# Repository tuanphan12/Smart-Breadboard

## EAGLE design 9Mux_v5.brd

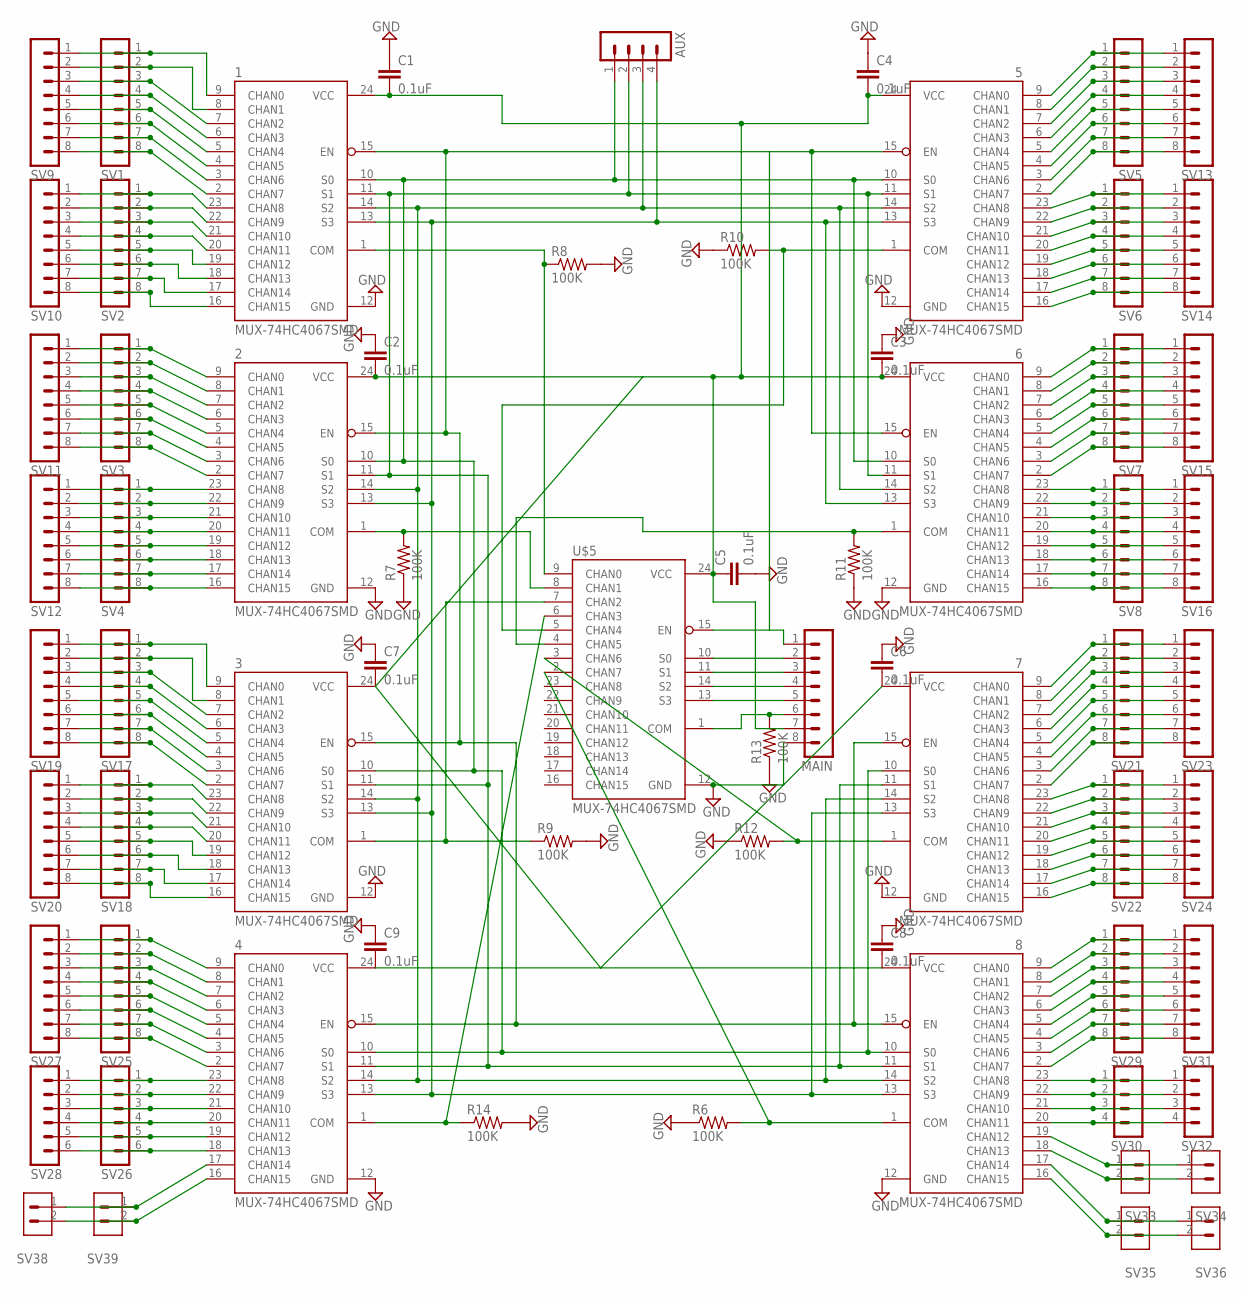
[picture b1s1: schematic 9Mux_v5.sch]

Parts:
1, 2, 3, 4, 5, 6, 7, 8: MUX-74HC4067SMD; SSOP24
AUX: MA04-1
C1, C2, C3, C4, C5, C6, C7, C8, C9: 0.1uF; 0603-CAP
MAIN: MA08-1
R6, R7, R8, R9, R10, R11, R12, R13, R14: 100K; 0603-RES
SV1, SV2, SV3, SV4, SV5, SV6, SV7, SV8, SV9, SV10, SV11, SV12, SV13, SV14, SV15, SV16, SV17, SV18, SV19, SV20, SV21, SV22, SV23, SV24, SV25, SV27, SV29, SV31: MA08-1
SV26, SV28: MA06-1
SV30, SV32: MA04-1
SV33, SV34, SV35, SV36, SV38, SV39: MA02-1; MA03-1
U$5: MUX-74HC4067SMD; SSOP24

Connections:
GND: 1.12 (GND), 2.12 (GND), 3.12 (GND), 4.12 (GND), 5.12 (GND), 6.12 (GND), 7.12 (GND), 8.12 (GND), C1.1, C2.1, C3.1, C4.1, C5.2, C6.1, C7.1, C8.1, C9.1, MAIN.8, R6.1, R7.1, R8.2, R9.2, R10.1, R11.1, R12.1, R13.1, R14.2, U$5.12 (GND)
MAIN: 1.11 (S1), 2.11 (S1), 3.11 (S1), 4.11 (S1), 5.11 (S1), 6.11 (S1), 7.11 (S1), 8.11 (S1), AUX.2
unnamed: 1.9 (CHAN0), SV1.1, SV9.1
unnamed: 1.8 (CHAN1), SV1.2, SV9.2
unnamed: 1.16 (CHAN15), SV2.8, SV10.8
unnamed: 1.17 (CHAN14), SV2.7, SV10.7
unnamed: 1.18 (CHAN13), SV2.6, SV10.6
unnamed: 2.8 (CHAN1), SV3.2, SV11.2
unnamed: 1.19 (CHAN12), SV2.5, SV10.5
unnamed: 1.20 (CHAN11), SV2.4, SV10.4
unnamed: 1.21 (CHAN10), SV2.3, SV10.3
unnamed: 1.22 (CHAN9), SV2.2, SV10.2
unnamed: 1.23 (CHAN8), SV2.1, SV10.1
unnamed: 1.7 (CHAN2), SV1.3, SV9.3
unnamed: 1.6 (CHAN3), SV1.4, SV9.4
unnamed: 1.5 (CHAN4), SV1.5, SV9.5
unnamed: 1.4 (CHAN5), SV1.6, SV9.6
unnamed: 1.3 (CHAN6), SV1.7, SV9.7
unnamed: 1.2 (CHAN7), SV1.8, SV9.8
unnamed: 2.9 (CHAN0), SV3.1, SV11.1
unnamed: 2.7 (CHAN2), SV3.3, SV11.3
unnamed: 2.6 (CHAN3), SV3.4, SV11.4
unnamed: 2.5 (CHAN4), SV3.5, SV11.5
unnamed: 5.5 (CHAN4), SV5.5, SV13.5
unnamed: 2.4 (CHAN5), SV3.6, SV11.6
unnamed: 2.3 (CHAN6), SV3.7, SV11.7
unnamed: 2.2 (CHAN7), SV3.8, SV11.8
unnamed: 2.23 (CHAN8), SV4.1, SV12.1
unnamed: 2.22 (CHAN9), SV4.2, SV12.2
unnamed: 2.21 (CHAN10), SV4.3, SV12.3
unnamed: 2.20 (CHAN11), SV4.4, SV12.4
unnamed: 2.19 (CHAN12), SV4.5, SV12.5
unnamed: 2.18 (CHAN13), SV4.6, SV12.6
unnamed: 2.17 (CHAN14), SV4.7, SV12.7
unnamed: 2.16 (CHAN15), SV4.8, SV12.8
unnamed: 5.9 (CHAN0), SV5.1, SV13.1
unnamed: 5.8 (CHAN1), SV5.2, SV13.2
unnamed: 5.7 (CHAN2), SV5.3, SV13.3
unnamed: 5.6 (CHAN3), SV5.4, SV13.4
unnamed: 5.4 (CHAN5), SV5.6, SV13.6
unnamed: 5.3 (CHAN6), SV5.7, SV13.7
unnamed: 5.2 (CHAN7), SV5.8, SV13.8
unnamed: 5.23 (CHAN8), SV6.1, SV14.1
unnamed: 5.22 (CHAN9), SV6.2, SV14.2
unnamed: 5.21 (CHAN10), SV6.3, SV14.3
unnamed: 5.20 (CHAN11), SV6.4, SV14.4
unnamed: 5.19 (CHAN12), SV6.5, SV14.5
unnamed: 5.18 (CHAN13), SV6.6, SV14.6
unnamed: 5.17 (CHAN14), SV6.7, SV14.7
unnamed: 5.16 (CHAN15), SV6.8, SV14.8
unnamed: 6.9 (CHAN0), SV7.1, SV15.1
unnamed: 6.8 (CHAN1), SV7.2, SV15.2
unnamed: 6.7 (CHAN2), SV7.3, SV15.3
unnamed: 6.6 (CHAN3), SV7.4, SV15.4
unnamed: 6.5 (CHAN4), SV7.5, SV15.5
unnamed: 1.10 (S0), 2.10 (S0), 3.10 (S0), 4.10 (S0), 5.10 (S0), 6.10 (S0), 7.10 (S0), 8.10 (S0), AUX.1
unnamed: 6.4 (CHAN5), SV7.6, SV15.6
unnamed: 1.14 (S2), 2.14 (S2), 3.14 (S2), 4.14 (S2), 5.14 (S2), 6.14 (S2), 7.14 (S2), 8.14 (S2), AUX.3
unnamed: 6.3 (CHAN6), SV7.7, SV15.7
unnamed: 6.2 (CHAN7), SV7.8, SV15.8
unnamed: 6.23 (CHAN8), SV8.1, SV16.1
unnamed: 1.13 (S3), 2.13 (S3), 3.13 (S3), 4.13 (S3), 5.13 (S3), 6.13 (S3), 7.13 (S3), 8.13 (S3), AUX.4
unnamed: 1.15 (EN), 2.15 (EN), 3.15 (EN), 4.15 (EN), 5.15 (EN), 6.15 (EN), 7.15 (EN), 8.15 (EN), MAIN.1, U$5.15 (EN)
unnamed: 6.22 (CHAN9), SV8.2, SV16.2
unnamed: 6.21 (CHAN10), SV8.3, SV16.3
unnamed: 6.20 (CHAN11), SV8.4, SV16.4
unnamed: 6.19 (CHAN12), SV8.5, SV16.5
unnamed: 6.18 (CHAN13), SV8.6, SV16.6
unnamed: 6.17 (CHAN14), SV8.7, SV16.7
unnamed: 6.16 (CHAN15), SV8.8, SV16.8
unnamed: 1.1 (COM), R8.1, U$5.9 (CHAN0)
unnamed: 3.9 (CHAN0), SV17.1, SV19.1
unnamed: 3.8 (CHAN1), SV17.2, SV19.2
unnamed: 3.16 (CHAN15), SV18.8, SV20.8
unnamed: 2.1 (COM), R7.2, U$5.8 (CHAN1)
unnamed: 6.1 (COM), R11.2, U$5.4 (CHAN5)
unnamed: 5.1 (COM), R10.2, U$5.5 (CHAN4)
unnamed: MAIN.2, U$5.10 (S0)
unnamed: MAIN.3, U$5.11 (S1)
unnamed: MAIN.4, U$5.14 (S2)
unnamed: MAIN.5, U$5.13 (S3)
unnamed: MAIN.6, R13.2, U$5.1 (COM)
unnamed: 3.17 (CHAN14), SV18.7, SV20.7
unnamed: 3.18 (CHAN13), SV18.6, SV20.6
unnamed: 3.19 (CHAN12), SV18.5, SV20.5
unnamed: 3.20 (CHAN11), SV18.4, SV20.4
unnamed: 3.21 (CHAN10), SV18.3, SV20.3
unnamed: 3.22 (CHAN9), SV18.2, SV20.2
unnamed: 3.23 (CHAN8), SV18.1, SV20.1
unnamed: 3.7 (CHAN2), SV17.3, SV19.3
unnamed: 3.6 (CHAN3), SV17.4, SV19.4
unnamed: 3.5 (CHAN4), SV17.5, SV19.5
unnamed: 3.4 (CHAN5), SV17.6, SV19.6
unnamed: 3.3 (CHAN6), SV17.7, SV19.7
unnamed: 3.2 (CHAN7), SV17.8, SV19.8
unnamed: 7.9 (CHAN0), SV21.1, SV23.1
unnamed: 7.8 (CHAN1), SV21.2, SV23.2
unnamed: 7.7 (CHAN2), SV21.3, SV23.3
unnamed: 7.6 (CHAN3), SV21.4, SV23.4
unnamed: 7.5 (CHAN4), SV21.5, SV23.5
unnamed: 7.4 (CHAN5), SV21.6, SV23.6
unnamed: 7.3 (CHAN6), SV21.7, SV23.7
unnamed: 7.2 (CHAN7), SV21.8, SV23.8
unnamed: 7.23 (CHAN8), SV22.1, SV24.1
unnamed: 7.22 (CHAN9), SV22.2, SV24.2
unnamed: 7.21 (CHAN10), SV22.3, SV24.3
unnamed: 7.20 (CHAN11), SV22.4, SV24.4
unnamed: 7.19 (CHAN12), SV22.5, SV24.5
unnamed: 7.18 (CHAN13), SV22.6, SV24.6
unnamed: 7.17 (CHAN14), SV22.7, SV24.7
unnamed: 7.16 (CHAN15), SV22.8, SV24.8
unnamed: 4.9 (CHAN0), SV25.1, SV27.1
unnamed: 4.8 (CHAN1), SV25.2, SV27.2
unnamed: 4.7 (CHAN2), SV25.3, SV27.3
unnamed: 4.6 (CHAN3), SV25.4, SV27.4
unnamed: 4.5 (CHAN4), SV25.5, SV27.5
unnamed: 4.4 (CHAN5), SV25.6, SV27.6
unnamed: 4.3 (CHAN6), SV25.7, SV27.7
unnamed: 4.2 (CHAN7), SV25.8, SV27.8
unnamed: 4.23 (CHAN8), SV26.1, SV28.1
unnamed: 4.22 (CHAN9), SV26.2, SV28.2
unnamed: 4.21 (CHAN10), SV26.3, SV28.3
unnamed: 4.20 (CHAN11), SV26.4, SV28.4
unnamed: 4.19 (CHAN12), SV26.5, SV28.5
unnamed: 4.18 (CHAN13), SV26.6, SV28.6
unnamed: 4.17 (CHAN14), SV38.1, SV39.1
unnamed: 4.16 (CHAN15), SV38.2, SV39.2
unnamed: 8.9 (CHAN0), SV29.1, SV31.1
unnamed: 8.8 (CHAN1), SV29.2, SV31.2
unnamed: 8.7 (CHAN2), SV29.3, SV31.3
unnamed: 8.6 (CHAN3), SV29.4, SV31.4
unnamed: 8.5 (CHAN4), SV29.5, SV31.5
unnamed: 8.4 (CHAN5), SV29.6, SV31.6
unnamed: 8.3 (CHAN6), SV29.7, SV31.7
unnamed: 8.2 (CHAN7), SV29.8, SV31.8
unnamed: 8.23 (CHAN8), SV30.1, SV32.1
unnamed: 8.22 (CHAN9), SV30.2, SV32.2
unnamed: 8.21 (CHAN10), SV30.3, SV32.3
unnamed: 8.20 (CHAN11), SV30.4, SV32.4
unnamed: 3.1 (COM), R9.1, U$5.7 (CHAN2)
unnamed: 7.1 (COM), R12.2, U$5.3 (CHAN6)
unnamed: 4.1 (COM), R14.1, U$5.6 (CHAN3)
unnamed: 8.1 (COM), R6.2, U$5.2 (CHAN7)
unnamed: 1.24 (VCC), 2.24 (VCC), 3.24 (VCC), 4.24 (VCC), 5.24 (VCC), 6.24 (VCC), 7.24 (VCC), 8.24 (VCC), C1.2, C2.2, C3.2, C4.2, C5.1, C6.2, C7.2, C8.2, C9.2, MAIN.7, U$5.24 (VCC)
unnamed: 8.19 (CHAN12), SV33.1, SV34.1
unnamed: 8.18 (CHAN13), SV33.2, SV34.2
unnamed: 8.17 (CHAN14), SV35.1, SV36.1
unnamed: 8.16 (CHAN15), SV35.2, SV36.2

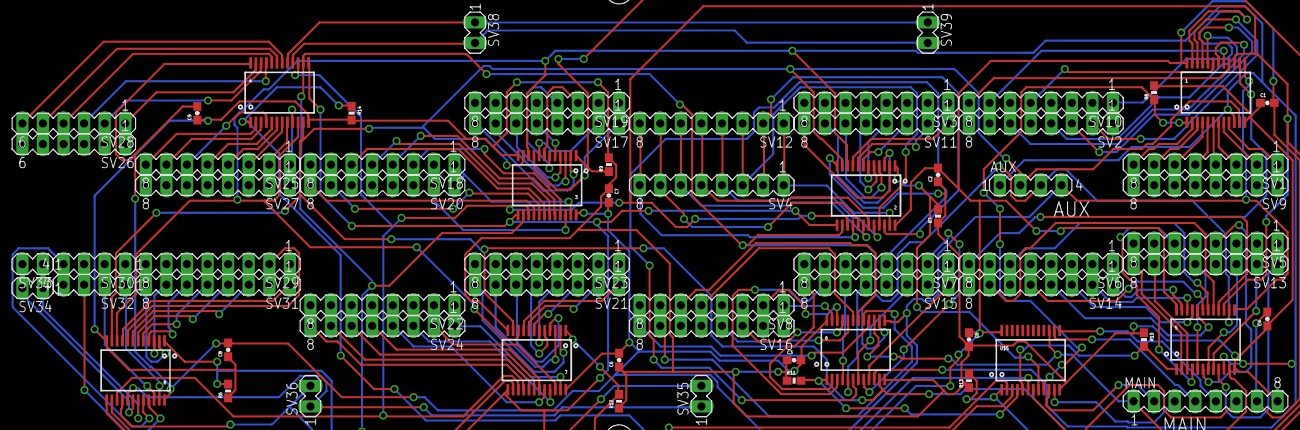
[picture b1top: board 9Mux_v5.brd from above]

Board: 2 copper layers, 67 parts (0 on the bottom side), 148 nets.

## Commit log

2017-04-04 documentation file
2017-04-04 added some comments to the teensy code
2017-04-04 reorganization
2017-04-04 added the schematic and the board files. Also the Gerber files
2017-04-04 new files
2017-04-04 update documentation
2017-04-05 changes in Teensy Breakout Board
2017-04-05 changes in the codes
2017-04-05 added the drill profile for the Gerber file
2017-04-05 updated documentation
2017-04-05 newer version to run continuously
2017-04-05 update 4/5/2017
2017-04-07 updates to the code. Can now graph using bokeh
2017-04-07 tidying up the codes a bit
2017-04-11 update with current items, 4/11/2017
2017-05-04 latest update 5/4/2017
2017-05-16 all changes as of 5/16/2017
2017-05-22 added laser cuts
2017-06-04 testing as of 6/4/17
2017-06-25 Adding some experimental data
2017-07-18 an attempt to use div_render
2017-07-18 latest lasercut
2017-07-18 I forgot to commit this one
2017-07-18 I forgot to push this one
2017-07-18 interface_dev adding for organizational purposes
2017-07-18 got Tuans code working
2017-07-19 updating rendering
2017-07-20 adding Joe's working code
2017-08-05 added the assembling instructions
2017-08-25 latest
2017-08-25 adding in joes working copy of code and python...auto connect to teensy 4Hz run rate/page updating
2017-09-05 files
2017-09-05 adding in ws2
2017-09-05 updating bokeh 12.7
2017-09-10 added datasheet of the 16 channel mux
2017-09-16 add Latex Documentation for the Breadboard! Yay! Nicer looking
2017-09-16 new experiments thing
2017-09-19 The code is working if you put the data directly into the file, I haven't had the chance to do some sort of import/export scheme yet
2018-05-30 rezipped file
2018-05-30 trying again
2018-05-30 rezip file

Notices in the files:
parts and their libraries:
SparkFun-AnalogIC: Licensing:Creative Commons ShareAlike 4.0 International - https://creativecommons.org/licenses/by-sa/4.0
